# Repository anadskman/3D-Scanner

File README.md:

# Portable 3D Scanner

A custom-designed portable 3D scanner built from scratch in Fusion 360 and KiCad. The scanner uses a motorised arch and rotating turntable to capture objects from different angles and create 3D models.

The design uses an ESP32, two NEMA 17 stepper motors, DRV8825 drivers and a 1080p USB camera.

## Overview

The scanner uses two motorised axes:

- Rotating turntable to move the object
- Motorised arch to move the camera around the object

The camera captures images from different angles while the ESP32 controls the movement of both motors.

The USB camera connects directly to a computer, where the images can be processed into a 3D model.

The main goal is to create a compact scanner that can be transported easily and used to scan smaller objects.

## Features

- Fully custom CAD design
- Custom designed PCB
- Motorised rotating turntable
- Motorised camera arch
- Internal gear mechanism
- 1080p USB camera
- WS2812 LED lighting
- Automatic homing using limit switches
- ESP32 motor control
- 3D printed components
- Modular and detachable components
- Designed to be portable

## Design Process

### Initial Concept

The original idea was to make a portable 3D scanner using a rotating turntable and a camera mounted on a curved arch.

Instead of moving multiple cameras around the object, the design uses one camera that can move to different positions while the turntable rotates.

The main parts were designed in Fusion 360, with the electronics designed separately in KiCad.

### Arch Mechanism

The arch holds the camera and allows it to move around the object.

The design uses an internal gear system to move the camera along the arch using a NEMA 17 stepper motor.

The arch includes:

- Internal gear teeth
- NEMA 17 motor mounting
- Camera mounting bracket
- Detachable mounting points
- Space for cable routing

The gear teeth were generated using Helix Gear+ in Fusion 360 rather than modelling each tooth individually.

### Turntable

The turntable rotates the object during scanning.

It uses a separate NEMA 17 stepper motor controlled by a DRV8825 driver.

The turntable is designed to hold smaller objects while keeping them centred during rotation.

### Camera Mount

The camera mount was designed specifically around the InnoMaker USB camera.

It attaches to the moving arch and holds the camera in position while allowing it to point towards the centre of the turntable.

### PCB Housing

A custom housing was designed for the PCB.

The housing includes cutouts for the barrel jack, screw terminals and connectors. It also has mounting holes for attaching the top and bottom sections together.

The ESP32 is removable rather than permanently enclosed inside the case.

## Electronics

### Components

- ESP32 Development Board
- 2× DRV8825 Stepper Drivers
- 2× NEMA 17 Stepper Motors
- InnoMaker 1080p USB Camera
- WS2812 RGB LED Ring
- 3× Limit Switches
- 12V Power Supply
- 5V Buck Converter
- Custom PCB

### PCB

The PCB was designed in KiCad and exported as a STEP model so it could be imported into Fusion 360.

This allowed the electronics to be placed into the mechanical assembly to check clearances and mounting positions.

## CAD Improvements

Several improvements were made throughout the design:

- Custom internal gear mechanism
- Modular motor mounts
- Detachable arch assembly
- Custom camera mount
- PCB housing with removable ESP32
- Standardised screw sizes
- STEP exports for individual components
- Full assembly with joints for movement testing
- PCB uploaded into Fusion 360 for clearance checking

## Bill of Materials

| **Name** | **Purpose** | **Quantity Purchased** | **Quantity Used** | **Link** | **Total Cost (EUR)** | **Distributor** |
| -------- | ----------- | --------------------- | ----------------- | -------------------- | -------- | --------------- |
| InnoMaker 1080p USB Camera | Captures images of the object | 1 | 1 | [Amazon](https://www.amazon.ie/gp/product/B0CNCSFQC1/ref=ox_sc_act_title_5?smid=A3LR51RN935ZZX&psc=1) | €20.92  | Amazon |
| NEMA 17 Stepper Motors | Drives the turntable and arch | 3 | 2 | [Amazon](https://www.amazon.ie/gp/product/B0FSPZT9P4/ref=ox_sc_act_title_4?smid=A3JL2PT0MX26A6&psc=1) | €27.00 | Amazon |
| WS2812 LED Rings | Provides lighting around the object | 5 | 1 | [Amazon](https://www.amazon.ie/gp/product/B0CMW5LWM2/ref=ox_sc_act_title_3?smid=A35XDNP896ERNI&psc=1) | €8.19 | Amazon |
| Limit Switches | Used for homing and movement limits | 3 | 3 | [Amazon](https://www.amazon.ie/Official-Switch-3-Piece-Compatible-Printers/dp/B09R3TWDSV/ref=sr_1_20?sr=8-20) | €4.99  | Amazon |
| ESP32 Development Board | Main controller for the scanner | 1 | 1 | [Amazon](https://www.amazon.ie/DollaTek-Development-Bluetooth-compatible-Ultra-Low-Consumption/dp/B0CXT3978J/ref=rvi_d_sccl_16/257-0773453-0872007?psc=1) | 7.99  | Amazon |
| DRV8825 Stepper Drivers | Controls the NEMA 17 motors | 2 | 2 | Owned | Owned | Owned |
| Custom PCB | Connects the electronics together | 1 | 1 | [JlCPCB](https://cart.jlcpcb.com/quote/gerberviewThree/?qs=2035bd6f6bf045a4be76bd0e8a033c01_1_0_1_0_0.html) | €22.63 | JlCPCB |
| 12V DC Power Supply | Main power for the scanner | 1 | 1 | Owned | Owned | Owned |
| 5V Buck Converter | Converts 12V to 5V for the ESP32 and LEDs | 1 | 1 | [Amazon](https://www.amazon.ie/Converter-Adjustable-Voltage-Efficient-Regulator/dp/B0FLYNNNWL/ref=sr_1_1?sr=8-1) | €8.99 | Amazon |
| 74AHCT125 | Logic level shifting for the LED data signal | 1 | 1 | [Amazon](https://www.amazon.ie/Be-Your-Mind-SN74AHCT125N-Three-State/dp/B0DXK7PWTN/ref=sr_1_1?sr=8-1) | €9.49 | Amazon |
| 330Ω Resistor | LED data line protection | 1 | 1 | Owned | Owned | Owned |
| 1000µF Capacitor | Smooths the LED power supply | 1 | 1 | Owned | Owned | Owned |
| 100µF Capacitors | Filters power near the stepper drivers | 2 | 2 | Owned | Owned | Owned |
| 100nF Capacitors | Decoupling for the electronics | 2+ | 2+ | Owned | Owned | Owned |
| Barrel Jack | Main power input | 1 | 1 | Owned | Owned | Owned |
| Screw Terminals / Connectors | Connects motors and power wiring | As required | As required | Owned | Owned | Owned |
| Fuse | Protects the main power input | 1 | 1 | [Amazon](https://www.amazon.ie/SeKi-Micro-Fuse-Glass-Fuses/dp/B09JZHQYR6/ref=sr_1_2?sr=8-2) | €6.88 | Amazon |
| Fuse Holder | Holds the fuse | 1 | 1 | [Amazon](https://www.amazon.ie/ECSiNG-Holder-Transparent-Terminals-5x20mm/dp/B0C4983C7C/ref=sr_1_2?sr=8-2) | €7.49 | Amazon |
| SB540 Schottky diode | reverse polarary protection | 1 | 1 | [Amazon](https://www.amazon.ie/20-Pieces-SR540-Schottky-Rectifier/dp/B079KDRFY7/ref=sr_1_2?sr=8-2) | €6.26  | Amazon |
**Total** **€130.83**

Prices are for the full packs purchased, not the cost of only the parts used. The third stepper motor and spare LED rings are included in the purchase quantities.

## Project Images

### CAD

### PCB

### Schematic

---

**Designed and built by Jason Clark**

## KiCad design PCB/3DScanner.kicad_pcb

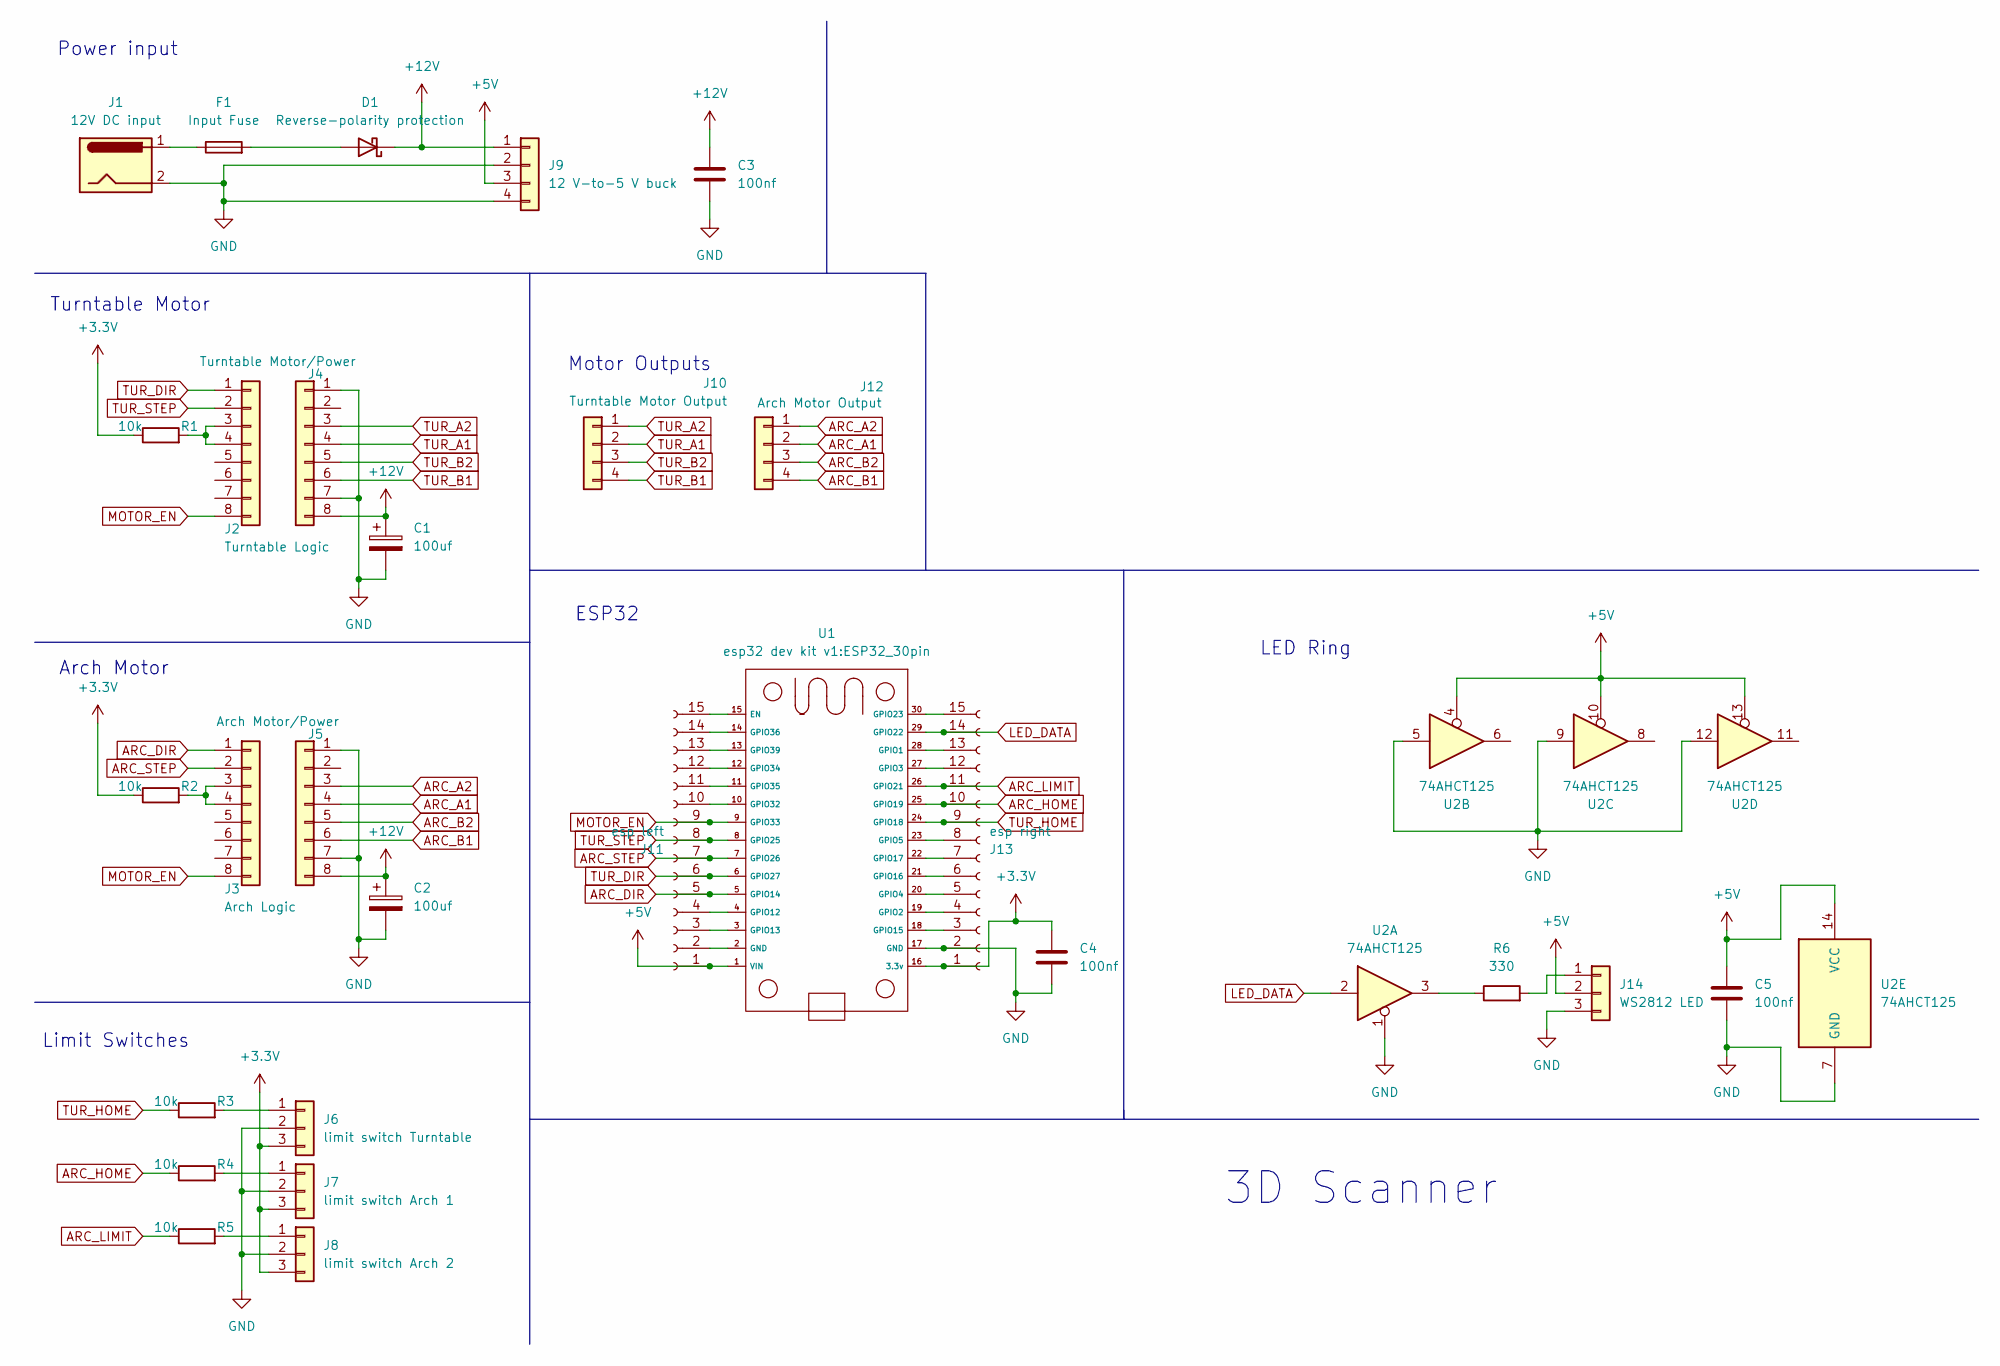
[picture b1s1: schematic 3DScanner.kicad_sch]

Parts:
C1, C2: 100uf; CP_Radial_D5.0mm_P2.00mm
C3, C4, C5: 100nf; CP_Radial_D10.0mm_P5.00mm
D1: Reverse-polarity protection; D_DO-41_SOD81_P10.16mm_Horizontal
F1: Input Fuse; Fuseholder_Clip-5x20mm_Bel_FC-203-22_Lateral_P17.80x5.00mm_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
J1: 12V DC input; BarrelJack_Horizontal
J2: Turntable Logic; PinSocket_1x08_P2.54mm_Vertical
J3: Arch Logic; PinSocket_1x08_P2.54mm_Vertical
J4: Turntable Motor/Power; PinSocket_1x08_P2.54mm_Vertical
J5: Arch Motor/Power; PinSocket_1x08_P2.54mm_Vertical
J6: limit switch Turntable; PinHeader_1x03_P2.54mm_Vertical
J7: limit switch Arch 1; PinHeader_1x03_P2.54mm_Vertical
J8: limit switch Arch 2; PinHeader_1x03_P2.54mm_Vertical
J9: 12 V-to-5 V buck; FanPinHeader_1x04_P2.54mm_Vertical
J10: Turntable Motor Output; TerminalBlock_Xinya_XY308-2.54-4P_1x04_P2.54mm_Horizontal
J11: esp left; PinSocket_1x15_P2.54mm_Vertical
J12: Arch Motor Output; TerminalBlock_Xinya_XY308-2.54-4P_1x04_P2.54mm_Horizontal
J13: esp right; PinSocket_1x15_P2.54mm_Vertical
J14: WS2812 LED; PinHeader_1x03_P2.54mm_Vertical
R1, R2, R3, R4, R5: 10k; R_Axial_DIN0207_L6.3mm_D2.5mm_P7.62mm_Horizontal
R6: 330; R_Axial_DIN0207_L6.3mm_D2.5mm_P7.62mm_Horizontal
U1: ESP32_30pin
U2: 74AHCT125; DIP-14_W7.62mm

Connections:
+3.3V: C4.1, J6.3 (VIN), J7.3 (VIN), J8.3 (VIN), J13.1, R1.1, R2.1, U1.16 (3.3v)
+5V: C5.1, J9.3, J11.1, J14.2 (+5V), U1.1 (VIN), U2.4, U2.10, U2.13, U2.14 (VCC)
+12V: C1.1, C2.1, C3.1, D1.1 (K), J4.8 (VMOT), J5.8 (VMOT), J9.1
ARC_A1: J5.4 (1A), J12.2
ARC_A2: J5.3 (2A), J12.1
ARC_B1: J5.6 (2B), J12.4
ARC_B2: J5.5 (1B), J12.3
ARC_DIR: J3.1 (Dir), J11.5, U1.5 (GPIO14)
ARC_HOME: J13.10, R4.1, U1.25 (GPIO19)
ARC_LIMIT: J13.11, R5.1, U1.26 (GPIO21)
ARC_STEP: J3.2 (STP), J11.7, U1.7 (GPIO26)
GND: C1.2, C2.2, C3.2, C4.2, C5.2, J1.2, J4.1 (GND), J4.7 (GND), J5.1 (GND), J5.7 (GND), J6.2 (GND), J7.2 (GND), J8.2 (GND), J9.2, J9.4, J13.2, J14.3 (GND), U1.17 (GND), U2.1, U2.5, U2.7 (GND), U2.9, U2.12
LED_DATA: J13.14, U1.29 (GPIO22), U2.2
MOTOR_EN: J2.8 (EN), J3.8 (EN), J11.9, U1.9 (GPIO33)
unnamed: D1.2 (A), F1.2
unnamed: F1.1, J1.1
unnamed: J2.3 (SLP), J2.4 (RST), R1.2
unnamed: J3.3 (SLP), J3.4 (RST), R2.2
unnamed: J6.1 (TUR_HOME), R3.2
unnamed: J7.1 (ARC_HOME), R4.2
unnamed: J8.1 (ARC_LIMIT), R5.2
unnamed: J11.2, U1.2 (GND)
unnamed: J11.3, U1.3 (GPIO13)
unnamed: J11.4, U1.4 (GPIO12)
unnamed: J11.10, U1.10 (GPIO32)
unnamed: J11.11, U1.11 (GPIO35)
unnamed: J11.12, U1.12 (GPIO34)
unnamed: J11.13, U1.13 (GPIO39)
unnamed: J11.14, U1.14 (GPIO36)
unnamed: J11.15, U1.15 (EN)
unnamed: J13.3, U1.18 (GPIO15)
unnamed: J13.4, U1.19 (GPIO2)
unnamed: J13.5, U1.20 (GPIO4)
unnamed: J13.6, U1.21 (GPIO16)
unnamed: J13.7, U1.22 (GPIO17)
unnamed: J13.8, U1.23 (GPIO5)
unnamed: J13.12, U1.27 (GPIO3)
unnamed: J13.13, U1.28 (GPIO1)
unnamed: J13.15, U1.30 (GPIO23)
unnamed: J14.1 (LED_DI), R6.2
unnamed: R6.1, U2.3
TUR_A1: J4.4 (1A), J10.2
TUR_A2: J4.3 (2A), J10.1
TUR_B1: J4.6 (2B), J10.4
TUR_B2: J4.5 (1B), J10.3
TUR_DIR: J2.1 (Dir), J11.6, U1.6 (GPIO27)
TUR_HOME: J13.9, R3.1, U1.24 (GPIO18)
TUR_STEP: J2.2 (STP), J11.8, U1.8 (GPIO25)

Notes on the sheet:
Turntable Motor
Motor Outputs
3D Scanner
Limit Switches
Arch Motor
Power input
ESP32
LED Ring

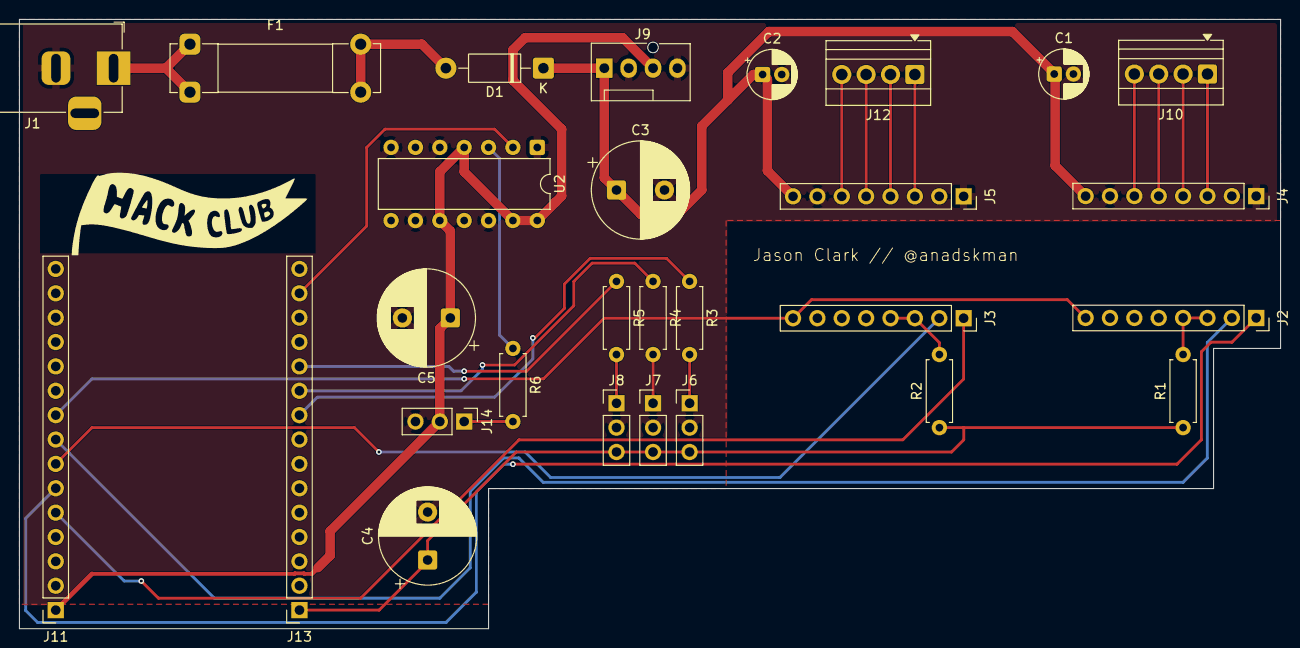
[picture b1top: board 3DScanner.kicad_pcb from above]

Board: 2 copper layers, 131.4 x 63.5 mm, 28 parts (0 on the bottom side), 30 nets.

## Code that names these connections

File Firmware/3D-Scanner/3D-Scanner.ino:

#include <AccelStepper.h>
#include <FastLED.h>

#define MOTOR_EN   33
#define TUR_STEP   25
#define ARC_STEP   26
#define TURN_DIR   27
#define ARC_DIR    14
#define LED_DATA   22
#define ARC_LIMIT  21
#define ARC_HOME   19
#define TURN_HOME  18
#define NUM_LEDS 12
CRGB leds[NUM_LEDS];

AccelStepper turntable(AccelStepper::DRIVER, TUR_STEP, TURN_DIR);
AccelStepper arch(AccelStepper::DRIVER, ARC_STEP, ARC_DIR);

const int TURN_HOME_DIRECTION = -1;
const int ARC_HOME_DIRECTION = -1;
const int SWITCH_ACTIVE = LOW;
const int MOTOR_ENABLED = LOW;
const int MOTOR_DISABLED = HIGH;
const float TURN_SPEED = 500;
const float ARC_SPEED = 300;
const unsigned long HOME_TIMEOUT = 30000;

bool motorsEnabled = false;

void enableMotors() {
  digitalWrite(MOTOR_EN, MOTOR_ENABLED);
  motorsEnabled = true;
  Serial.println("Motors enabled");
}

void disableMotors() {
  digitalWrite(MOTOR_EN, MOTOR_DISABLED);
  motorsEnabled = false;
  Serial.println("Motors disabled");
}

void stopMotors() {
  turntable.stop();
  arch.stop();
  Serial.println("Stopping motors");
}


bool turnHomePressed() {
  return digitalRead(TURN_HOME) == SWITCH_ACTIVE;
}

bool arcHomePressed() {
  return digitalRead(ARC_HOME) == SWITCH_ACTIVE;
}

bool arcLimitPressed() {
  return digitalRead(ARC_LIMIT) == SWITCH_ACTIVE;
}


bool homeTurntable() {
  Serial.println("Homing turntable...");

  if (turnHomePressed()) {
    turntable.setCurrentPosition(0);
    Serial.println("Turntable already at home");
    return true;
  }

  turntable.setSpeed(TURN_HOME_DIRECTION * 200);

  unsigned long startTime = millis();

  while (!turnHomePressed()) {
    turntable.runSpeed();

    if (millis() - startTime > HOME_TIMEOUT) {
      Serial.println("ERROR: Turntable homing timeout");
      turntable.setSpeed(0);
      return false;
    }

    delay(1);
  }

  turntable.setCurrentPosition(0);
  Serial.println("Turntable homed");
  return true;
}

bool homeArch() {
  Serial.println("Homing arch...");

  if (arcHomePressed()) {
    arch.setCurrentPosition(0);
    Serial.println("Arch already at home");
    return true;
  }

  arch.setSpeed(ARC_HOME_DIRECTION * 150);

  unsigned long startTime = millis();

  while (!arcHomePressed()) {
    if (arcLimitPressed()) {
      arch.setSpeed(0);
      Serial.println("ERROR: Arch limit reached while homing");
      return false;
    }

    arch.runSpeed();

    if (millis() - startTime > HOME_TIMEOUT) {
      arch.setSpeed(0);
      Serial.println("ERROR: Arch homing timeout");
      return false;
    }

    delay(1);
  }

  arch.setCurrentPosition(0);
  Serial.println("Arch homed");
  return true;
}

void homeAll() {
  enableMotors();

  if (!homeTurntable()) {
    disableMotors();
    return;
  }

  if (!homeArch()) {
    disableMotors();
    return;
  }

  Serial.println("All axes homed");
}

void moveTurntable(long steps) {
  enableMotors();

  turntable.move(steps);

  Serial.print("Turntable moving ");
  Serial.print(steps);
  Serial.println(" steps");
}

void moveArch(long steps) {
  enableMotors();

  if (steps > 0 && arcLimitPressed()) {
    Serial.println("Arch limit is pressed. Movement blocked.");
    return;
  }

  arch.move(steps);

  Serial.print("Arch moving ");
  Serial.print(steps);
  Serial.println(" steps");
}

void ledTest() {
  fill_solid(leds, NUM_LEDS, CRGB::Blue);
  FastLED.show();
  delay(500);

  fill_solid(leds, NUM_LEDS, CRGB::Green);
  FastLED.show();
  delay(500);

  fill_solid(leds, NUM_LEDS, CRGB::Red);
  FastLED.show();
  delay(500);

  FastLED.clear();
  FastLED.show();

  Serial.println("LED test complete");
}

void printHelp() {
  Serial.println();
  Serial.println("===== SCANNER CONTROL =====");
  Serial.println("T 2000   Turntable +2000 steps");
  Serial.println("T -2000  Turntable -2000 steps");
  Serial.println("A 1000   Arch +1000 steps");
  Serial.println("A -1000  Arch -1000 steps");
  Serial.println("HOME     Home both axes");
  Serial.println("STOP     Stop both motors");
  Serial.println("ON       Enable motors");
  Serial.println("OFF      Disable motors");
  Serial.println("LED      Test LED ring");
  Serial.println("STATUS   Show switch states");
  Serial.println("===========================");
  Serial.println();
}

void handleCommand(String command) {
  command.trim();
  command.toUpperCase();

  if (command == "HOME") {
    homeAll();
  }
  else if (command == "STOP") {
    stopMotors();
  }
  else if (command == "ON") {
    enableMotors();
  }
  else if (command == "OFF") {
    disableMotors();
  }
  else if (command == "LED") {
    ledTest();
  }
  else if (command == "STATUS") {
    Serial.print("Turn home: ");
    Serial.println(turnHomePressed() ? "PRESSED" : "OPEN");

    Serial.print("Arch home: ");
    Serial.println(arcHomePressed() ? "PRESSED" : "OPEN");

    Serial.print("Arch limit: ");
    Serial.println(arcLimitPressed() ? "PRESSED" : "OPEN");
  }
  else if (command.startsWith("T ")) {
    long steps = command.substring(2).toInt();
    moveTurntable(steps);
  }
  else if (command.startsWith("A ")) {
    long steps = command.substring(2).toInt();
    moveArch(steps);
  }
  else {
    Serial.println("Unknown command. Type HELP.");
  }
}

void setup() {
  Serial.begin(115200);

  pinMode(MOTOR_EN, OUTPUT);
  disableMotors();

  pinMode(TURN_HOME, INPUT_PULLUP);
  pinMode(ARC_HOME, INPUT_PULLUP);
  pinMode(ARC_LIMIT, INPUT_PULLUP);

  turntable.setMaxSpeed(TURN_SPEED);
  turntable.setAcceleration(300);

  arch.setMaxSpeed(ARC_SPEED);
  arch.setAcceleration(200);

  FastLED.addLeds<WS2812B, LED_DATA, GRB>(leds, NUM_LEDS);
  FastLED.setBrightness(80);
  FastLED.clear();
  FastLED.show();

  Serial.println();
  Serial.println("Portable 3D Scanner Firmware");
  Serial.println("ESP32 started successfully");

  printHelp();
}

void loop() {
  // Read serial commands.
  if (Serial.available()) {
    String command = Serial.readStringUntil('\n');
    handleCommand(command);
  }

  if (arcLimitPressed() && arch.distanceToGo() > 0) {
    arch.stop();
    Serial.println("WARNING: Arch limit reached");
  }

  turntable.run();
  arch.run();
}
